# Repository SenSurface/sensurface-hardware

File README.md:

# SenSurface Hardware

This repository contains hardwares schematics of SenSurface. 
The FT5316DME chip need a firmware to work, it is available here : <https://github.com/muca-board/muca-firmware>

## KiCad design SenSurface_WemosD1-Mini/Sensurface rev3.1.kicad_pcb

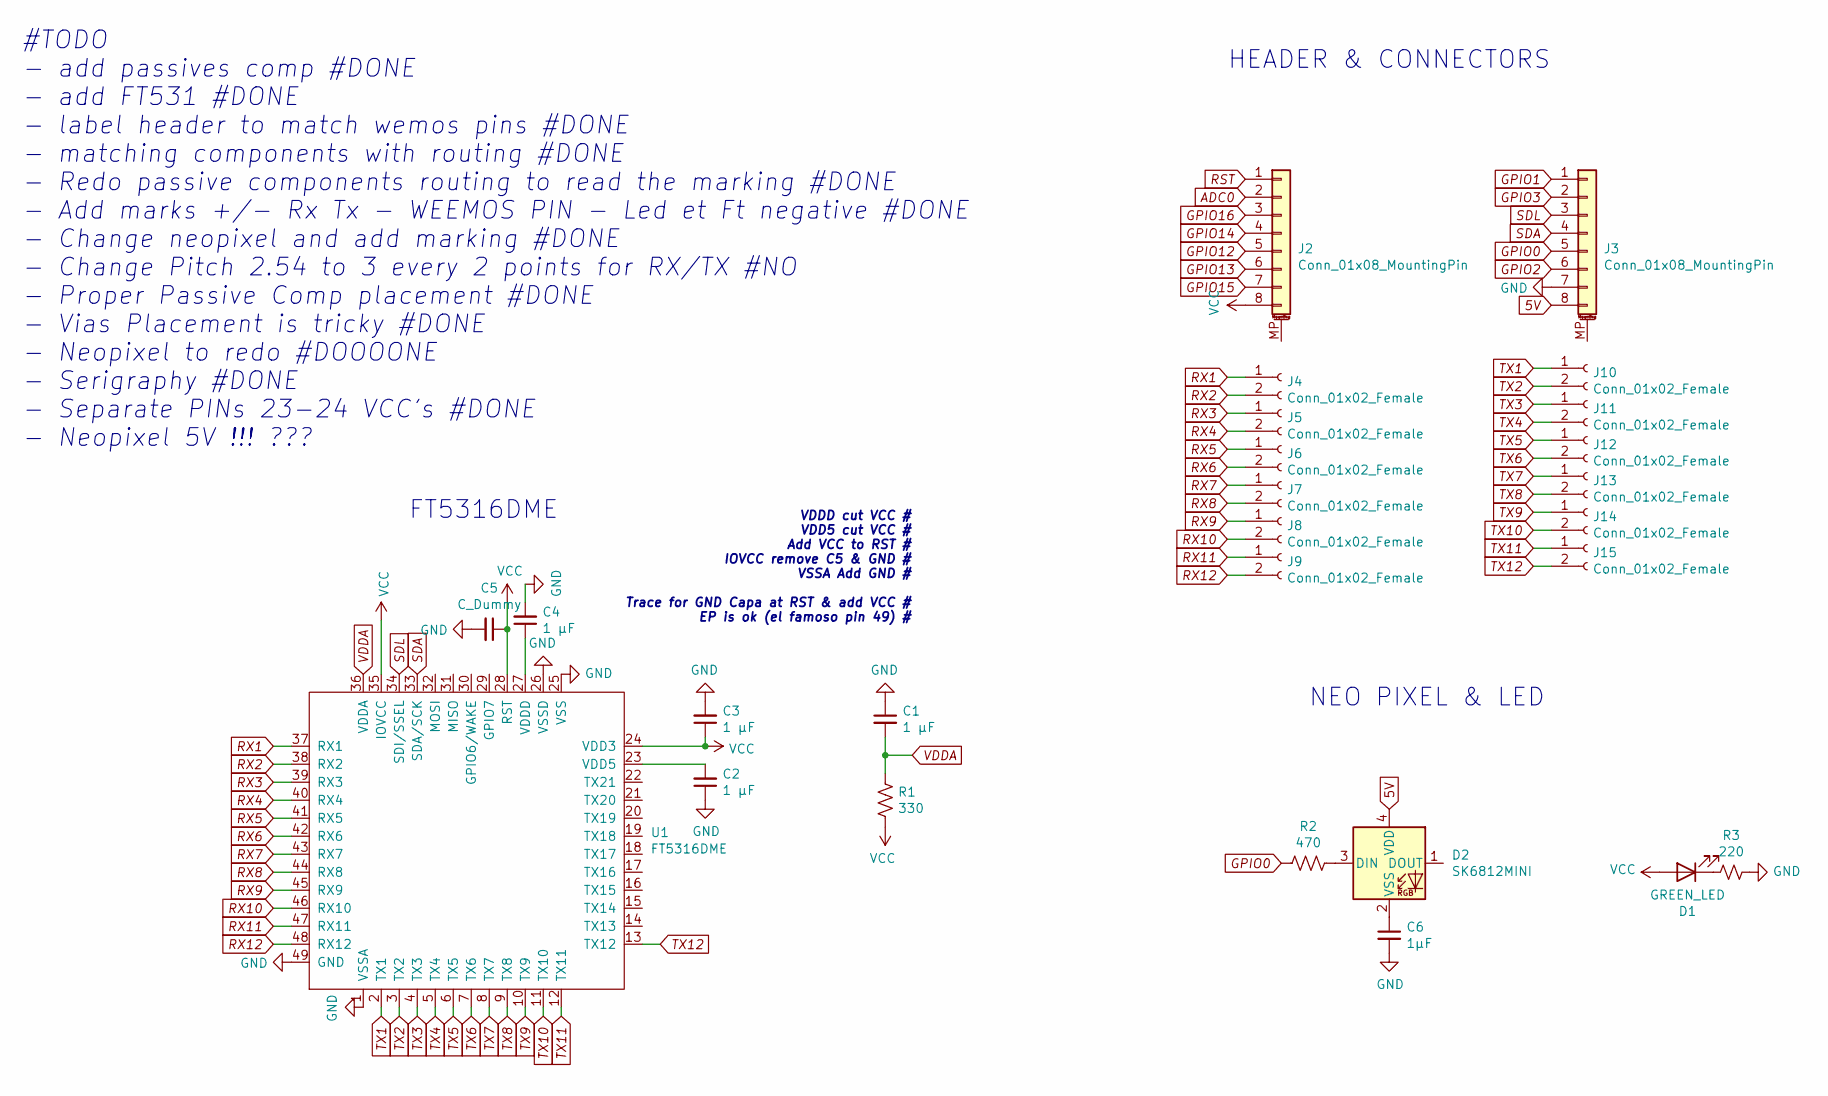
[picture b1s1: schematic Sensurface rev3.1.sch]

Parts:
C1, C2, C3, C4: 1 µF; C_0603_1608Metric
C5: C_Dummy; C_0603_1608Metric
C6: 1µF; C_0603_1608Metric
D1: GREEN_LED; LED_0805_2012Metric
D2: SK6812MINI; LED_SK6812MINI_PLCC4_3.5x3.5mm_P1.75mm
J2, J3: Conn_01x08_MountingPin; PinHeader_1x08_P2.54mm_Vertical
J4, J5, J6, J7, J8, J9, J10, J11, J12, J13, J14, J15: Conn_01x02_Female; TerminalBlock_Phoenix_MPT-0,5-2-2.54_1x02_P2.54mm_Horizontal
R1: 330; R_0603_1608Metric
R2: 470; R_0603_1608Metric
R3: 220; R_0603_1608Metric
U1: FT5316DME; QFN-48-1EP_6x6mm_P0.4mm_EP4.2x4.2mm

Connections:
5V: D2.4 (VDD), J3.8
ADC0: J2.2
GND: C1.1, C2.1, C3.2, C4.2, C5.2, C6.2, J3.7, R3.1, U1.1 (VSSA), U1.25 (VSS), U1.26 (VSSD), U1.49 (GND)
GPIO0: J3.5, R2.2
GPIO1: J3.1
GPIO2: J3.6
GPIO3: J3.2
GPIO12: J2.5
GPIO13: J2.6
GPIO14: J2.4
GPIO15: J2.7
GPIO16: J2.3
unnamed: C2.2, U1.23 (VDD5)
unnamed: C4.1, U1.27 (VDDD)
unnamed: C6.1, D2.2 (VSS)
unnamed: D1.1 (K), R3.2
unnamed: D2.3 (DIN), R2.1
RST: J2.1
RX1: J4.1, U1.37 (RX1)
RX2: J4.2, U1.38 (RX2)
RX3: J5.1, U1.39 (RX3)
RX4: J5.2, U1.40 (RX4)
RX5: J6.1, U1.41 (RX5)
RX6: J6.2, U1.42 (RX6)
RX7: J7.1, U1.43 (RX7)
RX8: J7.2, U1.44 (RX8)
RX9: J8.1, U1.45 (RX9)
RX10: J8.2, U1.46 (RX10)
RX11: J9.1, U1.47 (RX11)
RX12: J9.2, U1.48 (RX12)
SDA: J3.4, U1.33 (SDA/SCK)
SDL: J3.3, U1.34 (SDI/SSEL)
TX1: J10.1, U1.2 (TX1)
TX2: J10.2, U1.3 (TX2)
TX3: J11.1, U1.4 (TX3)
TX4: J11.2, U1.5 (TX4)
TX5: J12.1, U1.6 (TX5)
TX6: J12.2, U1.7 (TX6)
TX7: J13.1, U1.8 (TX7)
TX8: J13.2, U1.9 (TX8)
TX9: J14.1, U1.10 (TX9)
TX10: J14.2, U1.11 (TX10)
TX11: J15.1, U1.12 (TX11)
TX12: J15.2, U1.13 (TX12)
VCC: C3.1, C5.1, D1.2 (A), J2.8, R1.2, U1.24 (VDD3), U1.28 (RST), U1.35 (IOVCC)
VDDA: C1.2, R1.1, U1.36 (VDDA)

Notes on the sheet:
FT5316DME
HEADER & CONNECTORS
NEO PIXEL & LED
#TODO - add passives comp #DONE - add FT531 #DONE - label header to match wemos pins #DONE - matching components with routing #DONE - Redo passive components routing to read the marking #DONE - Add marks +/- Rx Tx - WEEMOS PIN - Led et Ft negative #DONE - Change neopixel and add marking #DONE - Cha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
VDDD cut VCC # VDD5 cut VCC # Add VCC to RST # IOVCC remove C5 & GND # VSSA Add GND # Trace for GND Capa at RST & add VCC # EP is ok (el famoso pin 49) #

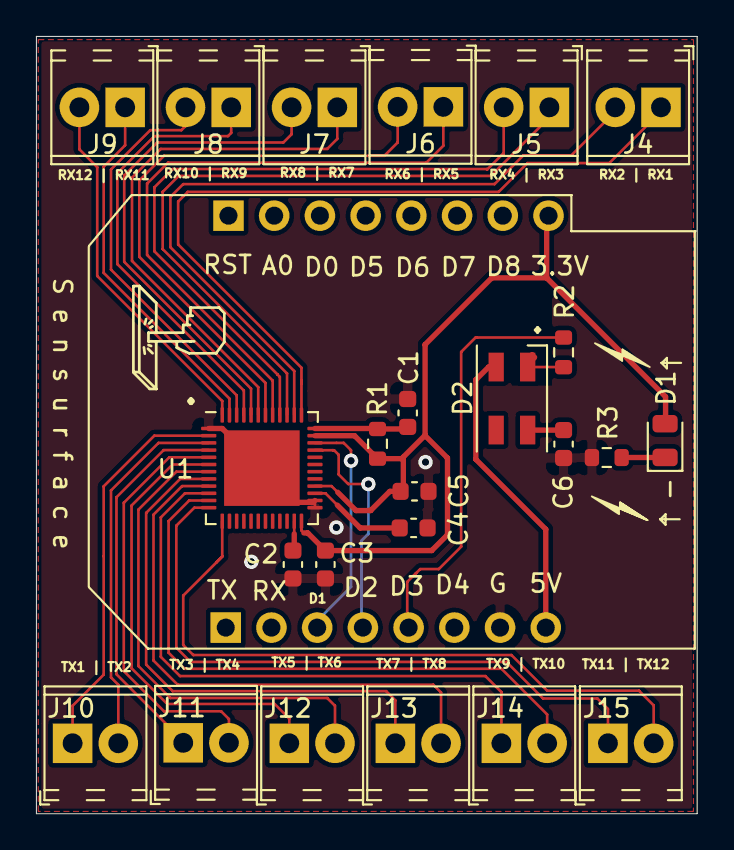
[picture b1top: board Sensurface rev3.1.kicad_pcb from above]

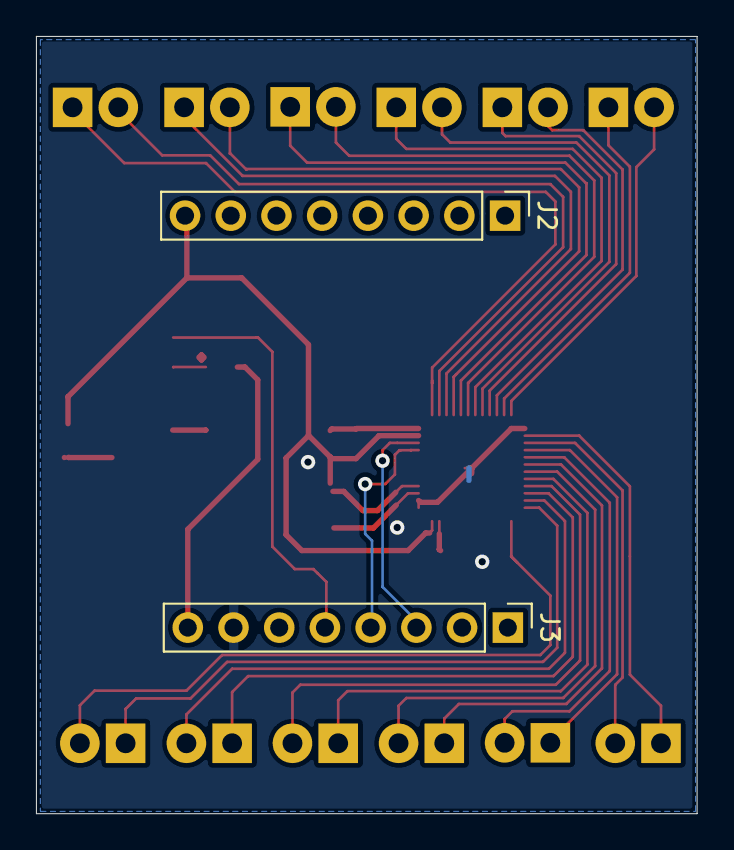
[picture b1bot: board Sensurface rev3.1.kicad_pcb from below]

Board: 2 copper layers, 36.7 x 43.2 mm, 26 parts (2 on the bottom side), 36 nets.

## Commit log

2022-04-21 ADD : SenSurface wemosd1_mini kicad + readme
